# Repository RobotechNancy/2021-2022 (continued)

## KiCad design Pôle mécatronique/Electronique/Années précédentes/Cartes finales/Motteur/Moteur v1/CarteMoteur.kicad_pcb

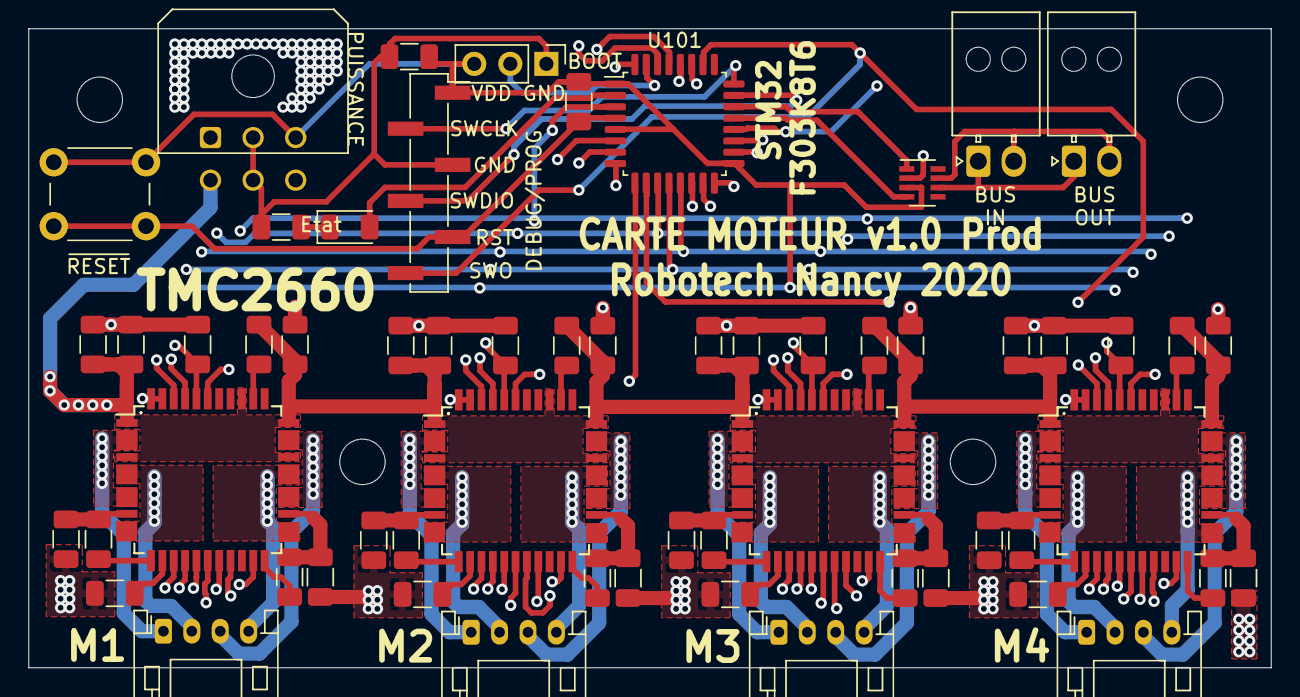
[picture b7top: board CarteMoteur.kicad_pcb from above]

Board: 4 copper layers, 87.5 x 45.0 mm, 64 parts (0 on the bottom side), 72 nets.

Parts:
BOOT1: Jumper_3_Open; PinHeader_1x03_P2.54mm_Vertical
C1, C2, C204, C205, C304, C305, C404, C405, C504, C505: 100nF; C_1206_3216Metric
C201, C301, C401, C501: 220nF; C_1206_3216Metric
C202, C203, C302, C303, C402, C403, C502, C503: 10uF; C_1206_3216Metric
C206, C306, C406, C506: 470nF; C_1206_3216Metric
D1: LED; LED_1206_3216Metric
DEBUG1: Conn_01x06; PinHeader_1x06_P2.54mm_Vertical_SMD_Pin1Right
H101, H102, H103, H104: MountingHole; MountingHole_3.2mm_M3_ISO7380
J101: Conn_02x03_Top_Bottom; Molex_Micro-Fit_3.0_43045-0600_2x03_P3.00mm_Horizontal
J102, J103: Conn_02x01; Molex_Nano-Fit_105313-xx02_1x02_P2.50mm_Horizontal
J201, J301, J401, J501: Conn_01x04; JST_PH_S4B-PH-K_1x04_P2.00mm_Horizontal
R1: R; R_1206_3216Metric
R201, R203, R301, R303, R401, R403, R501, R503: 0R075; R_1206_3216Metric
R202, R204, R302, R304, R402, R404, R502, R504: 10R; R_1206_3216Metric
SW1: SW_Push; SW_PUSH_6mm
U101: STM32F303K8Tx; LQFP-32_7x7mm_P0.8mm
U102: TCAN332; SOT-23-8
U201, U301, U401, U501: TMC2660-PA; TQFP-44_TCM2660-PA

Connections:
+3V3: BOOT1.3, C1.1, C2.1, C205.1, C305.1, C405.1, C505.1, DEBUG1.1, J101.3, SW1.1, U101.1, U101.5, U101.17, U102.3, U201.40, U301.40, U401.40, U501.40
+12V: C201.2, C202.1, C203.1, C204.1, C301.2, C302.1, C303.1, C304.1, C401.2, C402.1, C403.1, C404.1, C501.2, C502.1, C503.1, C504.1, J101.4, U201.1, U201.4, U201.30, U201.33, U201.36, U301.1, U301.4, U301.30, U301.33, U301.36, U401.1, U401.4, U401.30, U401.33, U401.36, U501.1, U501.4, U501.30, U501.33, U501.36
/C1: U101.27, U201.18
/C2: U101.8, U301.18
/C3: U101.10, U401.18
/C4: U101.19, U501.18
/CAN_RX: U101.21, U102.4
/CAN_TX: U101.22, U102.1
/CLK: U101.3, U201.21, U301.21, U401.21, U501.21
/D1: U101.29, U201.41
/D2: U101.7, U301.41
/D3: U101.15, U401.41
/D4: DEBUG1.4, U101.23, U501.41
/Driver TMC/A1: J201.1, U201.2, U201.7
/Driver TMC/A2: J201.2, U201.5, U201.10
/Driver TMC/B1: J201.3, U201.26, U201.31
/Driver TMC/B2: J201.4, U201.23, U201.28
/E1: U101.28, U201.19
/E2: U101.9, U301.19
/E3: U101.18, U401.19
/E4: U101.20, U501.19
/LED: D1.2, U101.2
/NRST: C1.2, DEBUG1.5, SW1.2, U101.4
/S1: U101.30, U201.42
/S2: U101.6, U301.42
/S3: U101.14, U401.42
/S4: DEBUG1.6, U101.26, U501.42
/SCK: U101.11, U201.16, U301.16, U401.16, U501.16
/SDI: U101.13, U201.15, U301.15, U401.15, U501.15
/SDO: U101.12, U201.14, U301.14, U401.14, U501.14
/SWCLK: DEBUG1.2, U101.24
/sheet5DF44EB7/A1: J301.1, U301.2, U301.7
/sheet5DF44EB7/A2: J301.2, U301.5, U301.10
/sheet5DF44EB7/B1: J301.3, U301.26, U301.31
/sheet5DF44EB7/B2: J301.4, U301.23, U301.28
/sheet5DF470E2/A1: J401.1, U401.2, U401.7
/sheet5DF470E2/A2: J401.2, U401.5, U401.10
/sheet5DF470E2/B1: J401.3, U401.26, U401.31
/sheet5DF470E2/B2: J401.4, U401.23, U401.28
/sheet5DF493B8/A1: J501.1, U501.2, U501.7
/sheet5DF493B8/A2: J501.2, U501.5, U501.10
/sheet5DF493B8/B1: J501.3, U501.26, U501.31
/sheet5DF493B8/B2: J501.4, U501.23, U501.28
GND: BOOT1.1, C2.2, C202.2, C203.2, C204.2, C205.2, C206.2, C302.2, C303.2, C304.2, C305.2, C306.2, C402.2, C403.2, C404.2, C405.2, C406.2, C502.2, C503.2, C504.2, C505.2, C506.2, DEBUG1.3, J101.2, J101.5, R1.1, R201.2, R203.2, R301.2, R303.2, R401.2, R403.2, R501.2, R503.2, U101.16, U101.32, U102.2, U201.17, U201.39, U201.43, U201.44, U301.17, U301.39, U301.43, U301.44, U401.17, U401.39, U401.43, U401.44, U501.17, U501.39, U501.43, U501.44
unnamed: BOOT1.2, U101.31
unnamed: C201.1, U201.35
unnamed: C206.1, U201.13
unnamed: C301.1, U301.35
unnamed: C306.1, U301.13
unnamed: C401.1, U401.35
unnamed: C406.1, U401.13
unnamed: C501.1, U501.35
unnamed: C506.1, U501.13
unnamed: D1.1, R1.2
unnamed: J102.1, J103.1, U102.6
unnamed: J102.2, J103.2, U102.7
unnamed: R201.1, R202.1, U201.9
unnamed: R202.2, U201.12
unnamed: R203.1, R204.1, U201.25
unnamed: R204.2, U201.22
unnamed: R301.1, R302.1, U301.9
unnamed: R302.2, U301.12
unnamed: R303.1, R304.1, U301.25
unnamed: R304.2, U301.22
unnamed: R401.1, R402.1, U401.9
unnamed: R402.2, U401.12
unnamed: R403.1, R404.1, U401.25
unnamed: R404.2, U401.22
unnamed: R501.1, R502.1, U501.9
unnamed: R502.2, U501.12
unnamed: R503.1, R504.1, U501.25
unnamed: R504.2, U501.22
